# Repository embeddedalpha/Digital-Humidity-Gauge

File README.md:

# Digital Humidity Gauge

## Version: 1.0.0

## Precisly Measure:

    🎯 Dry‑bulb Temperature                  
    🎯 Relative humidity            
    🎯 Barometric pressure         
    🎯 Saturation vapour pressure   
    🎯 Actual vapour pressure
    🎯 Humidity (mixing) ratio
    🎯 Absolute humidity
    🎯 Dew‑point temperature
    🎯 Wet‑bulb temperature
    🎯 Enthalpy
    🎯 Specific volume
    🎯 Moist‑air density

## Project Structure

```

    📁 Case
    📁 Firmware
    📁 Marketing and Documentation
    📁 Media
    📁 PCB
    📁 Software
    📁 Simulations
    📁 Wires and Cables
    📄 README.md

```

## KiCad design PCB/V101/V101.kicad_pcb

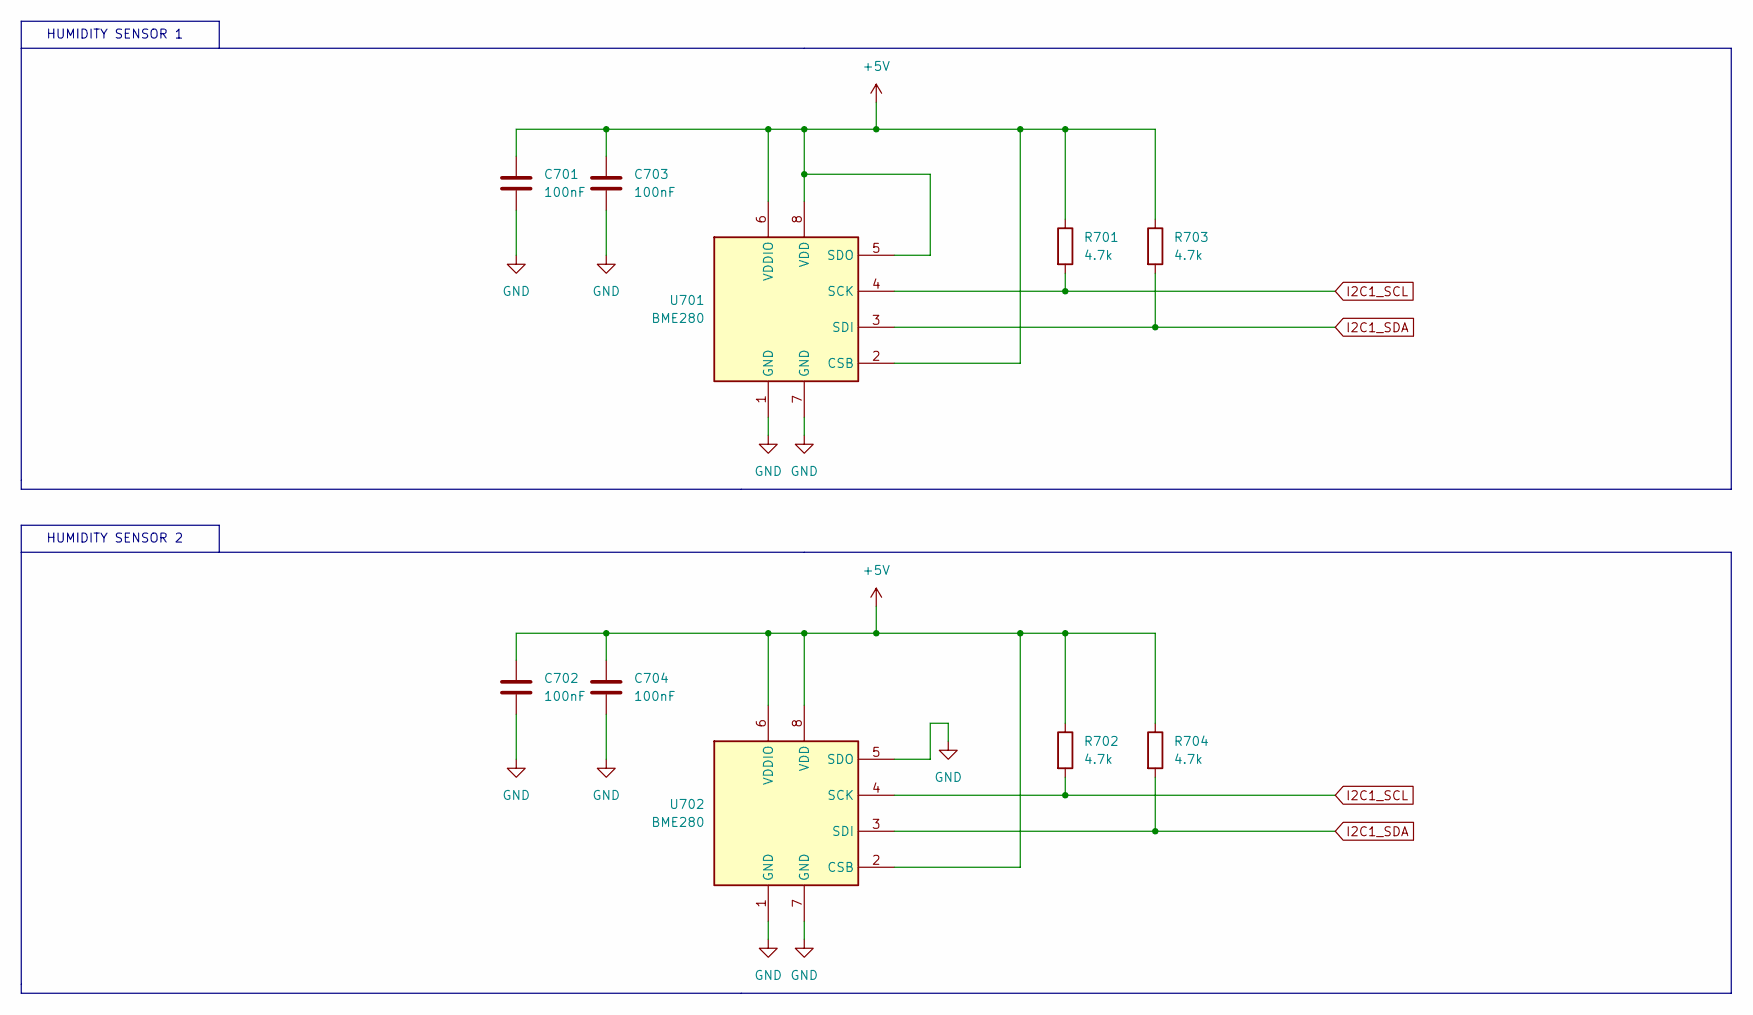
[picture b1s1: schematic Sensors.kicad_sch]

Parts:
C701, C702, C703, C704: 100nF; C_0603_1608Metric_Pad1.08x0.95mm_HandSolder
R701, R702, R703, R704: 4.7k; R_0603_1608Metric_Pad0.98x0.95mm_HandSolder
U701, U702: BME280; Bosch_LGA-8_2.5x2.5mm_P0.65mm_ClockwisePinNumbering

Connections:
+5V: C701.1, C702.1, C703.1, C704.1, R701.1, R702.1, R703.1, R704.1, U701.2 (CSB), U701.5 (SDO), U701.6 (VDDIO), U701.8 (VDD), U702.2 (CSB), U702.6 (VDDIO), U702.8 (VDD); also elsewhere on the board
GND: C701.2, C702.2, C703.2, C704.2, U701.1 (GND), U701.7 (GND), U702.1 (GND), U702.5 (SDO), U702.7 (GND); also elsewhere on the board
I2C1_SCL: R701.2, R702.2, U701.4 (SCK), U702.4 (SCK)
I2C1_SDA: R703.2, R704.2, U701.3 (SDI), U702.3 (SDI)

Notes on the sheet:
HUMIDITY SENSOR 1
HUMIDITY SENSOR 2

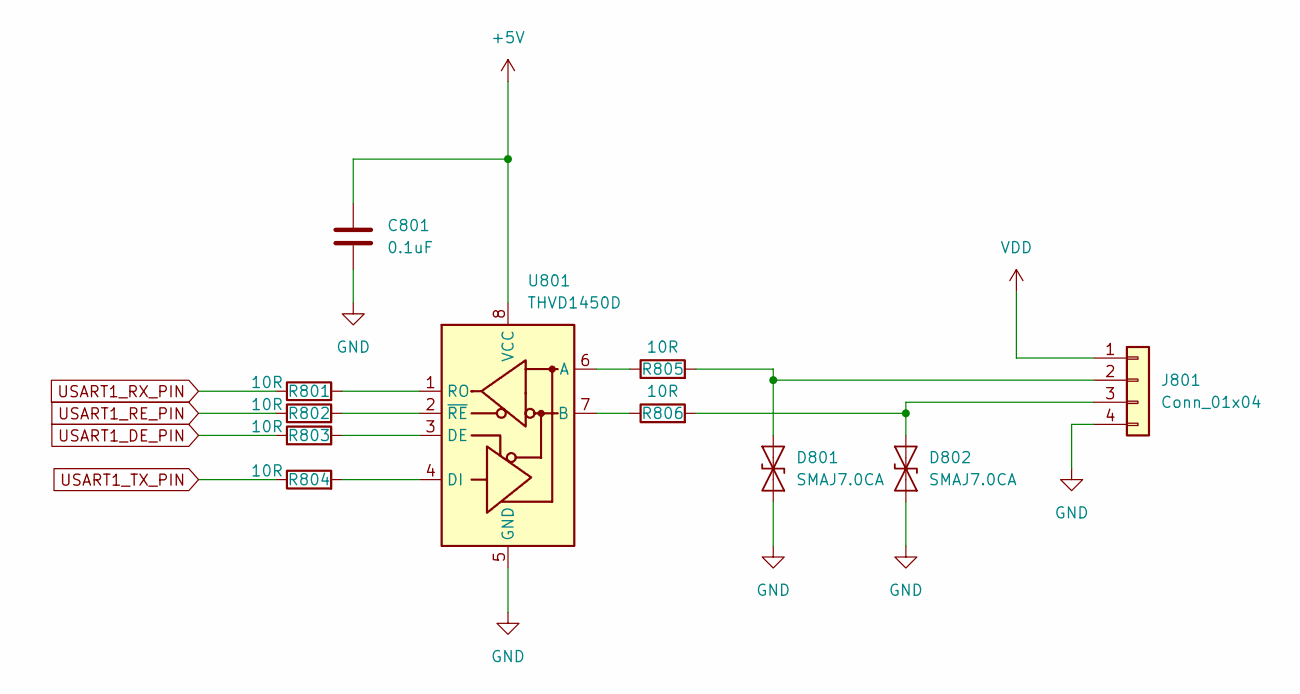
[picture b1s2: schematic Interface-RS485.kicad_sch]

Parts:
C801: 0.1uF; C_0603_1608Metric_Pad1.08x0.95mm_HandSolder
D801, D802: SMAJ7.0CA; D_SMA
J801: Conn_01x04; JST_PH_S4B-PH-K_1x04_P2.00mm_Horizontal
R801, R802, R803, R804, R805, R806: 10R; R_0603_1608Metric_Pad0.98x0.95mm_HandSolder
U801: THVD1450D; SOIC-8_3.9x4.9mm_P1.27mm

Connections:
+5V: C801.1, U801.8 (VCC); also elsewhere on the board
GND: C801.2, D801.1 (A1), D802.1 (A1), J801.4, U801.5 (GND); also elsewhere on the board
unnamed: D801.2 (A2), J801.2, R805.2
unnamed: D802.2 (A2), J801.3, R806.2
unnamed: R805.1, U801.6 (A)
unnamed: R806.1, U801.7 (B)
unnamed: R803.2, U801.3 (DE)
unnamed: R804.2, U801.4 (DI)
unnamed: R801.2, U801.1 (RO)
unnamed: R802.2, U801.2 (~RE)
USART1_DE_PIN: R803.1
USART1_RE_PIN: R802.1
USART1_RX_PIN: R801.1
USART1_TX_PIN: R804.1
VDD: J801.1; also elsewhere on the board

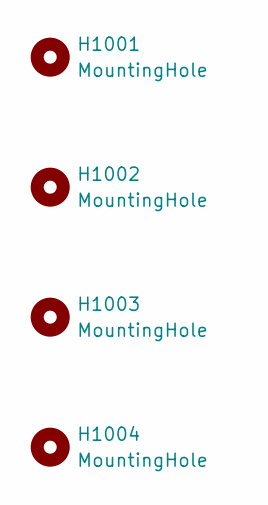
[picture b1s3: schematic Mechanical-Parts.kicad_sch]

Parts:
H1001, H1002, H1003, H1004: MountingHole; MountingHole_3.2mm_M3

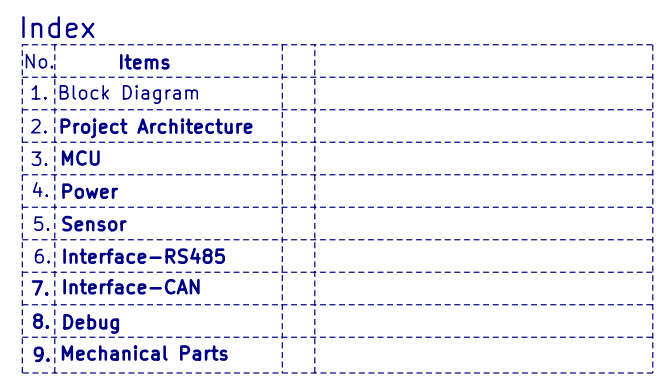
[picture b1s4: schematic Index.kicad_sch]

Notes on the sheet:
Mechanical Parts
Block Diagram
Power
Interface-RS485
Debug
Items
Interface-CAN
No.
MCU
Sensor
Project Architecture
Index

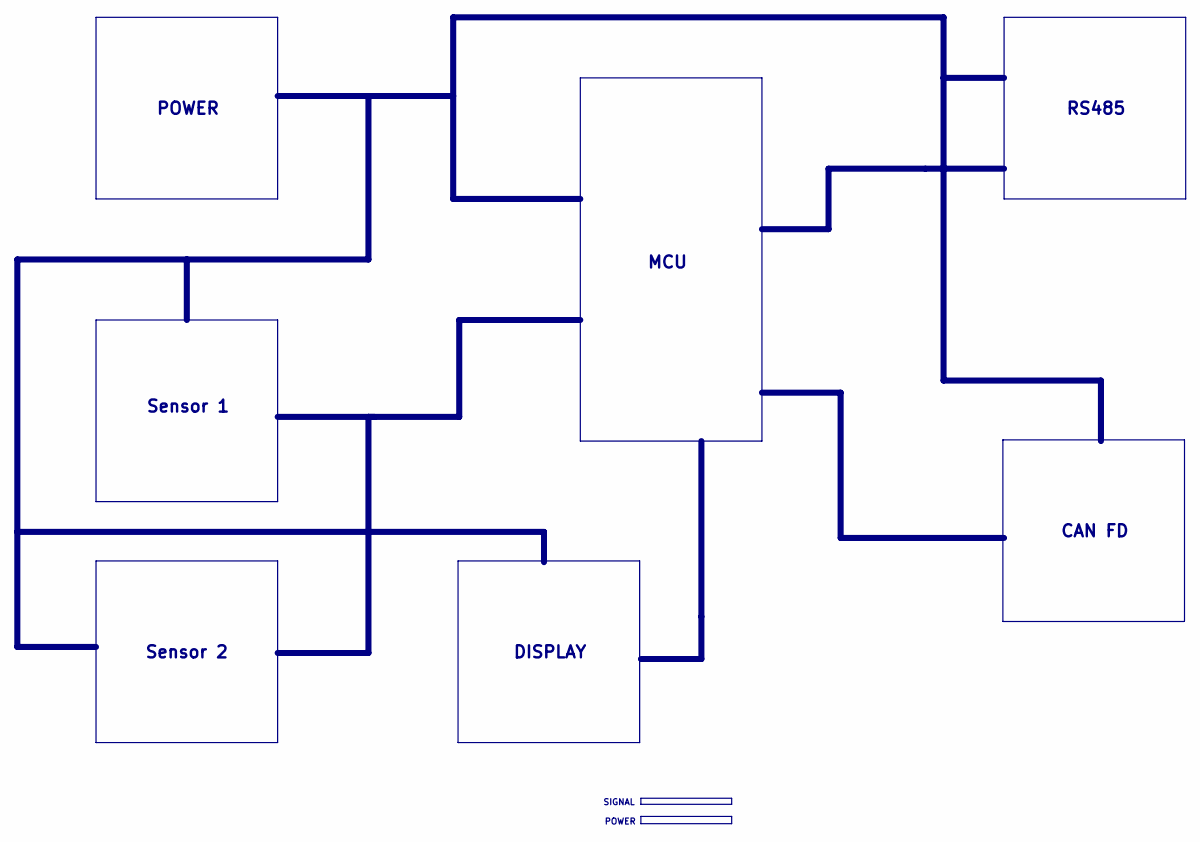
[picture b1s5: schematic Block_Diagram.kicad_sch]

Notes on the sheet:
Sensor 2
MCU
Sensor 1
RS485
SIGNAL
CAN FD
POWER
DISPLAY

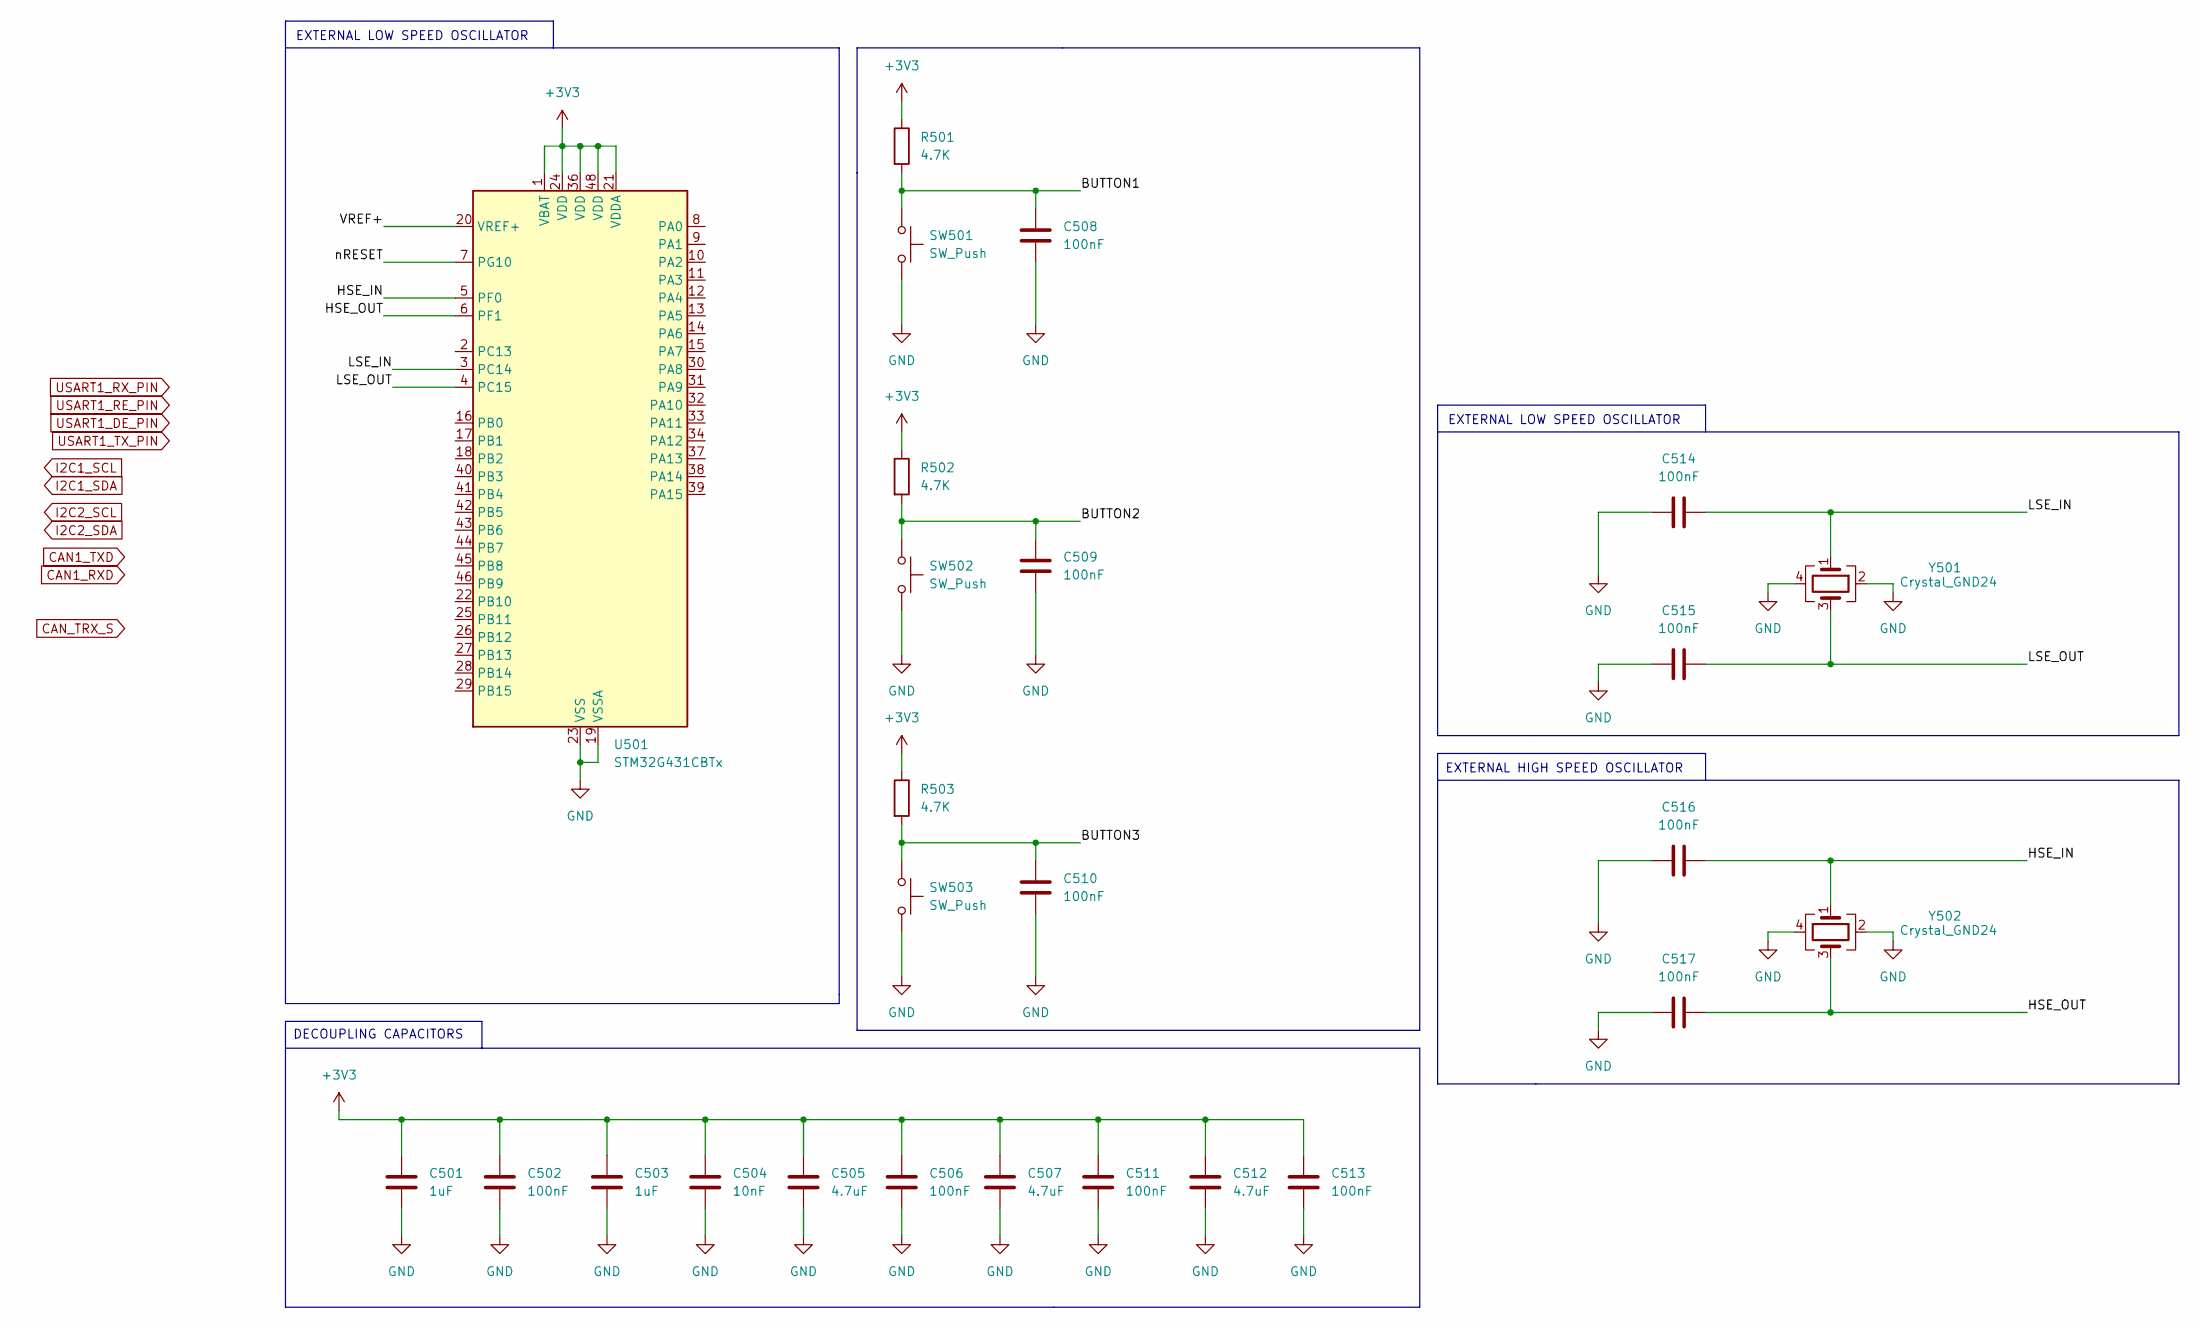
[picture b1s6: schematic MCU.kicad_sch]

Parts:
C501, C503: 1uF; C_0402_1005Metric_Pad0.74x0.62mm_HandSolder
C502, C506, C508, C509, C510, C511, C513, C514, C515, C516, C517: 100nF; C_0402_1005Metric_Pad0.74x0.62mm_HandSolder
C504: 10nF; C_0402_1005Metric_Pad0.74x0.62mm_HandSolder
C505, C507, C512: 4.7uF; C_0402_1005Metric_Pad0.74x0.62mm_HandSolder
R501, R502, R503: 4.7K; R_0603_1608Metric_Pad0.98x0.95mm_HandSolder
SW501, SW502, SW503: SW_Push
U501: STM32G431CBTx; LQFP-48_7x7mm_P0.5mm
Y501, Y502: Crystal_GND24

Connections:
+3V3: C501.1, C502.1, C503.1, C504.1, C505.1, C506.1, C507.1, C511.1, C512.1, C513.1, R501.1, R502.1, R503.1, U501.1 (VBAT), U501.21 (VDDA), U501.24 (VDD), U501.36 (VDD), U501.48 (VDD)
/MCU/BUTTON1: C508.1, R501.2, SW501.1
/MCU/BUTTON2: C509.1, R502.2, SW502.1
/MCU/BUTTON3: C510.1, R503.2, SW503.1
/MCU/HSE_IN: C516.1, U501.5 (PF0), Y502.1
/MCU/HSE_OUT: C517.1, U501.6 (PF1), Y502.3
/MCU/LSE_IN: C514.1, U501.3 (PC14), Y501.1
/MCU/LSE_OUT: C515.1, U501.4 (PC15), Y501.3
/MCU/VREF+: U501.20 (VREF+)
/MCU/nRESET: U501.7 (PG10)
GND: C501.2, C502.2, C503.2, C504.2, C505.2, C506.2, C507.2, C508.2, C509.2, C510.2, C511.2, C512.2, C513.2, C514.2, C515.2, C516.2, C517.2, SW501.2, SW502.2, SW503.2, U501.19 (VSSA), U501.23 (VSS), U501.35 (VSS), U501.47 (VSS), Y501.2, Y501.4, Y502.2, Y502.4; also elsewhere on the board

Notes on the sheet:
EXTERNAL LOW SPEED OSCILLATOR
DECOUPLING CAPACITORS
EXTERNAL HIGH SPEED OSCILLATOR

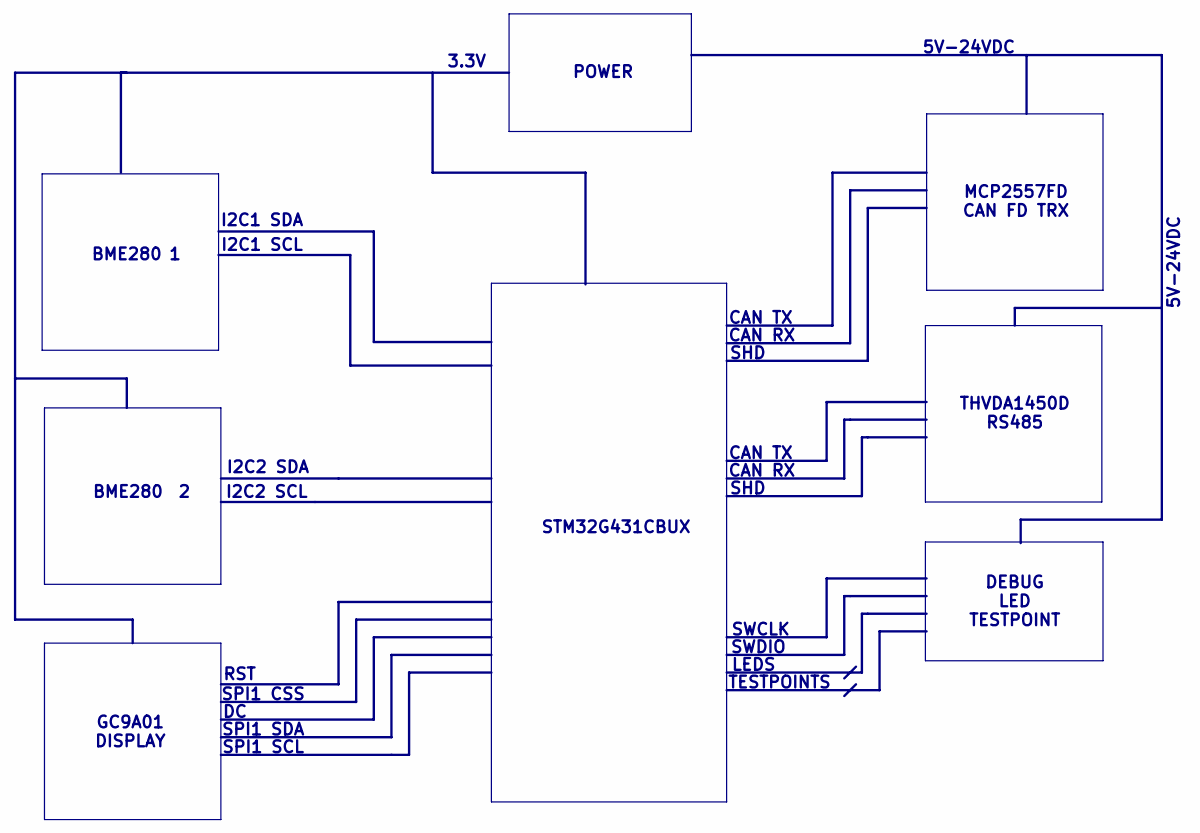
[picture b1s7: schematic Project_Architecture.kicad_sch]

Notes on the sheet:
POWER
RST
SWCLK
MCP2557FD CAN FD TRX
CAN RX
SPI1 SDA
SPI1 SCL
I2C2 SCL
I2C2 SDA
CAN TX
SHD
I2C1 SDA
TESTPOINTS
SWDIO
3.3V
STM32G431CBUX
GC9A01 DISPLAY
5V-24VDC
BME280
I2C1 SCL
SPI1 CSS
THVDA1450D RS485
LEDS
DEBUG LED TESTPOINT

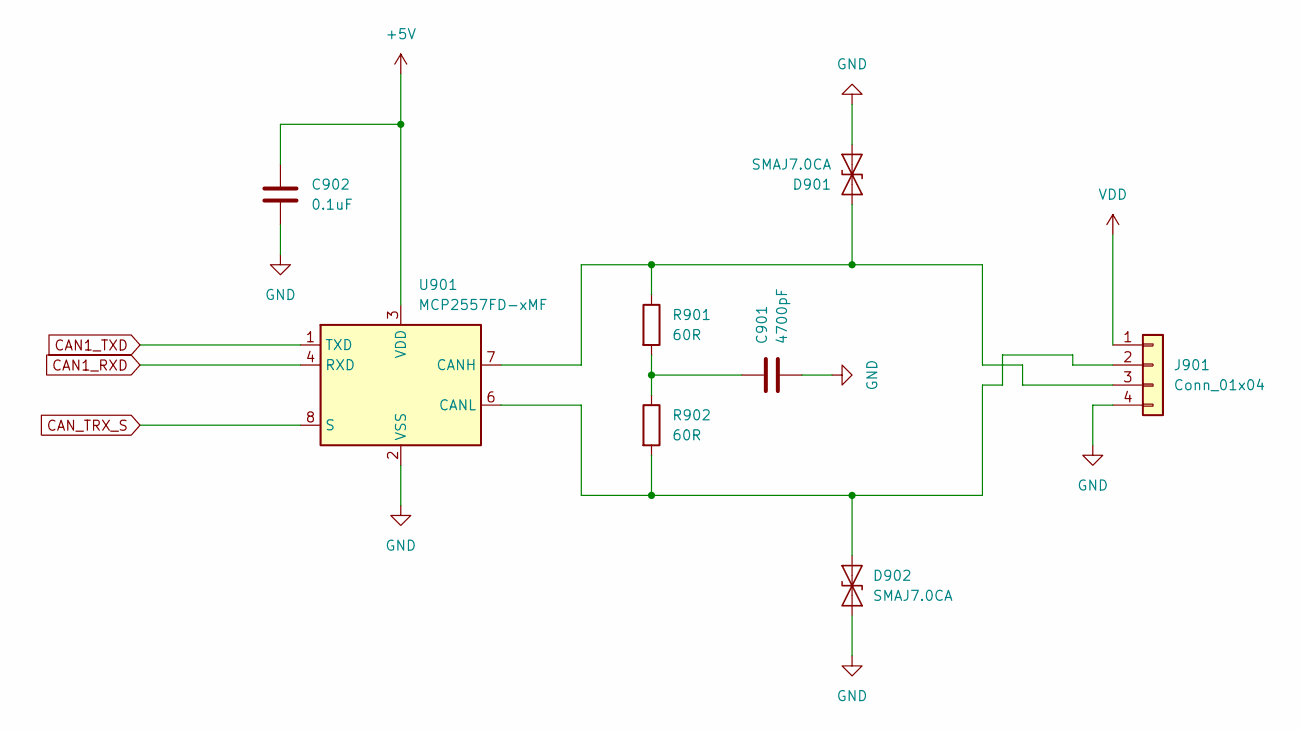
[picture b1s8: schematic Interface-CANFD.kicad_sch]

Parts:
C901: 4700pF; C_0603_1608Metric_Pad1.08x0.95mm_HandSolder
C902: 0.1uF; C_0603_1608Metric_Pad1.08x0.95mm_HandSolder
D901, D902: SMAJ7.0CA; D_SMA
J901: Conn_01x04; JST_PH_S4B-PH-K_1x04_P2.00mm_Horizontal
R901, R902: 60R; R_0603_1608Metric_Pad0.98x0.95mm_HandSolder
U901: MCP2557FD-xMF; DFN-8-1EP_3x3mm_P0.65mm_EP1.55x2.4mm

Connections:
+5V: C902.1, U901.3 (VDD); also elsewhere on the board
CAN1_RXD: U901.4 (RXD)
CAN1_TXD: U901.1 (TXD)
CAN_TRX_S: U901.8 (S)
GND: C901.2, C902.2, D901.1 (A1), D902.1 (A1), J901.4, U901.2 (VSS), U901.9 (VSS); also elsewhere on the board
unnamed: C901.1, R901.2, R902.1
unnamed: D901.2 (A2), J901.3, R901.1, U901.7 (CANH)
unnamed: D902.2 (A2), J901.2, R902.2, U901.6 (CANL)
VDD: J901.1; also elsewhere on the board

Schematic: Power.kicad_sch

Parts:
C601: 10uF; C_0603_1608Metric_Pad1.08x0.95mm_HandSolder
C602, C603: 0.1uF; C_0603_1608Metric_Pad1.08x0.95mm_HandSolder
C604, C605, C606: 22uF; C_0603_1608Metric_Pad1.08x0.95mm_HandSolder
L601: 10uH; L_APV_ANR5045
R601: 511K; R_0603_1608Metric_Pad0.98x0.95mm_HandSolder
R602: 105K; R_0603_1608Metric_Pad0.98x0.95mm_HandSolder
R603, R604, R605: R; R_0603_1608Metric_Pad0.98x0.95mm_HandSolder
U601: TPS54302; SOT-23-6

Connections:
5V: C604.1, C605.1, L601.2, R603.1
GND: C601.2, C602.2, C604.2, C605.2, R602.2, R605.2, U601.1 (GND); also elsewhere on the board
unnamed: C606.1, R603.2, R604.1
unnamed: C603.1, U601.6 (BOOT)
unnamed: R601.2, R602.1, U601.5 (EN)
unnamed: C606.2, R604.2, R605.1, U601.4 (FB)
unnamed: C603.2, L601.1, U601.2 (SW)
V_IN: C601.1, C602.1, R601.1, U601.3 (VIN)

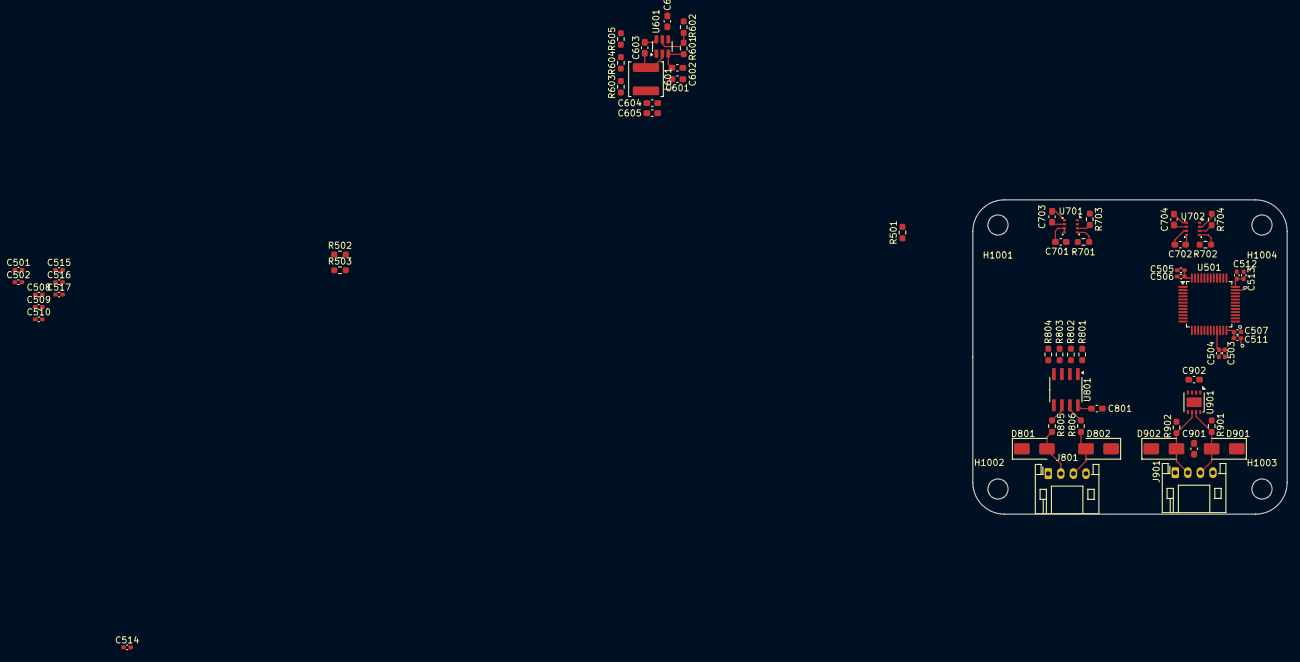
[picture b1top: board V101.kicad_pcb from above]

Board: 2 copper layers, 50.0 x 50.0 mm, 67 parts (0 on the bottom side), 31 nets.

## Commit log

2025-04-22 Added Firmware
2025-04-24 Updated Firmware - Needs Testing
2025-04-29 Updated Firmware Added SPI and GC9A01 Drivers
2025-04-30 Updated Firmware- GC9A01 Driver needs to be corrected and tested on new batch of screens
2025-05-01 Updated Firmware- SPI Driver Works but DMA needs to be rectified
2025-05-01 Updated Firmware- SPI Driver works and DMA is integrated
2025-05-03 Updated Firmware- W25Q Driver is started, everything works well
2025-05-04 Updated Firmware - Driver will be completed in a couple of days
2025-05-05 Updated Firmware - Data can be sent back and forth.
2025-05-06 updated repo
2025-05-06 Updated Devices
2025-05-06 Updated Driver- SPI and W25Qx works great now
2025-05-06 Added Filesystem
2025-05-07 Updated Repo- GC9a01 Driver needs testing
2025-05-07 GC9401 Driver can display images. Need to flash jpgegs on W25Q128
2025-05-09 Updated SPI Driver
2025-05-10 Updated Firmware
2025-05-14 Corrected Timer.c
2025-05-14 Updated BME280 Driver
2025-05-18 Added RTC
2025-05-19 Updated rtc
2025-05-20 Updated RTC Driver
2025-09-08 Added CAN Driver
2025-09-09 Updated Project
2025-10-11 Updated PCB with PA & Block Diagram
2025-10-11 Updated schematic
2025-10-14 Updated PCB
2025-10-15 Updated Layout
2025-10-15 Updated images and schematic pdf
